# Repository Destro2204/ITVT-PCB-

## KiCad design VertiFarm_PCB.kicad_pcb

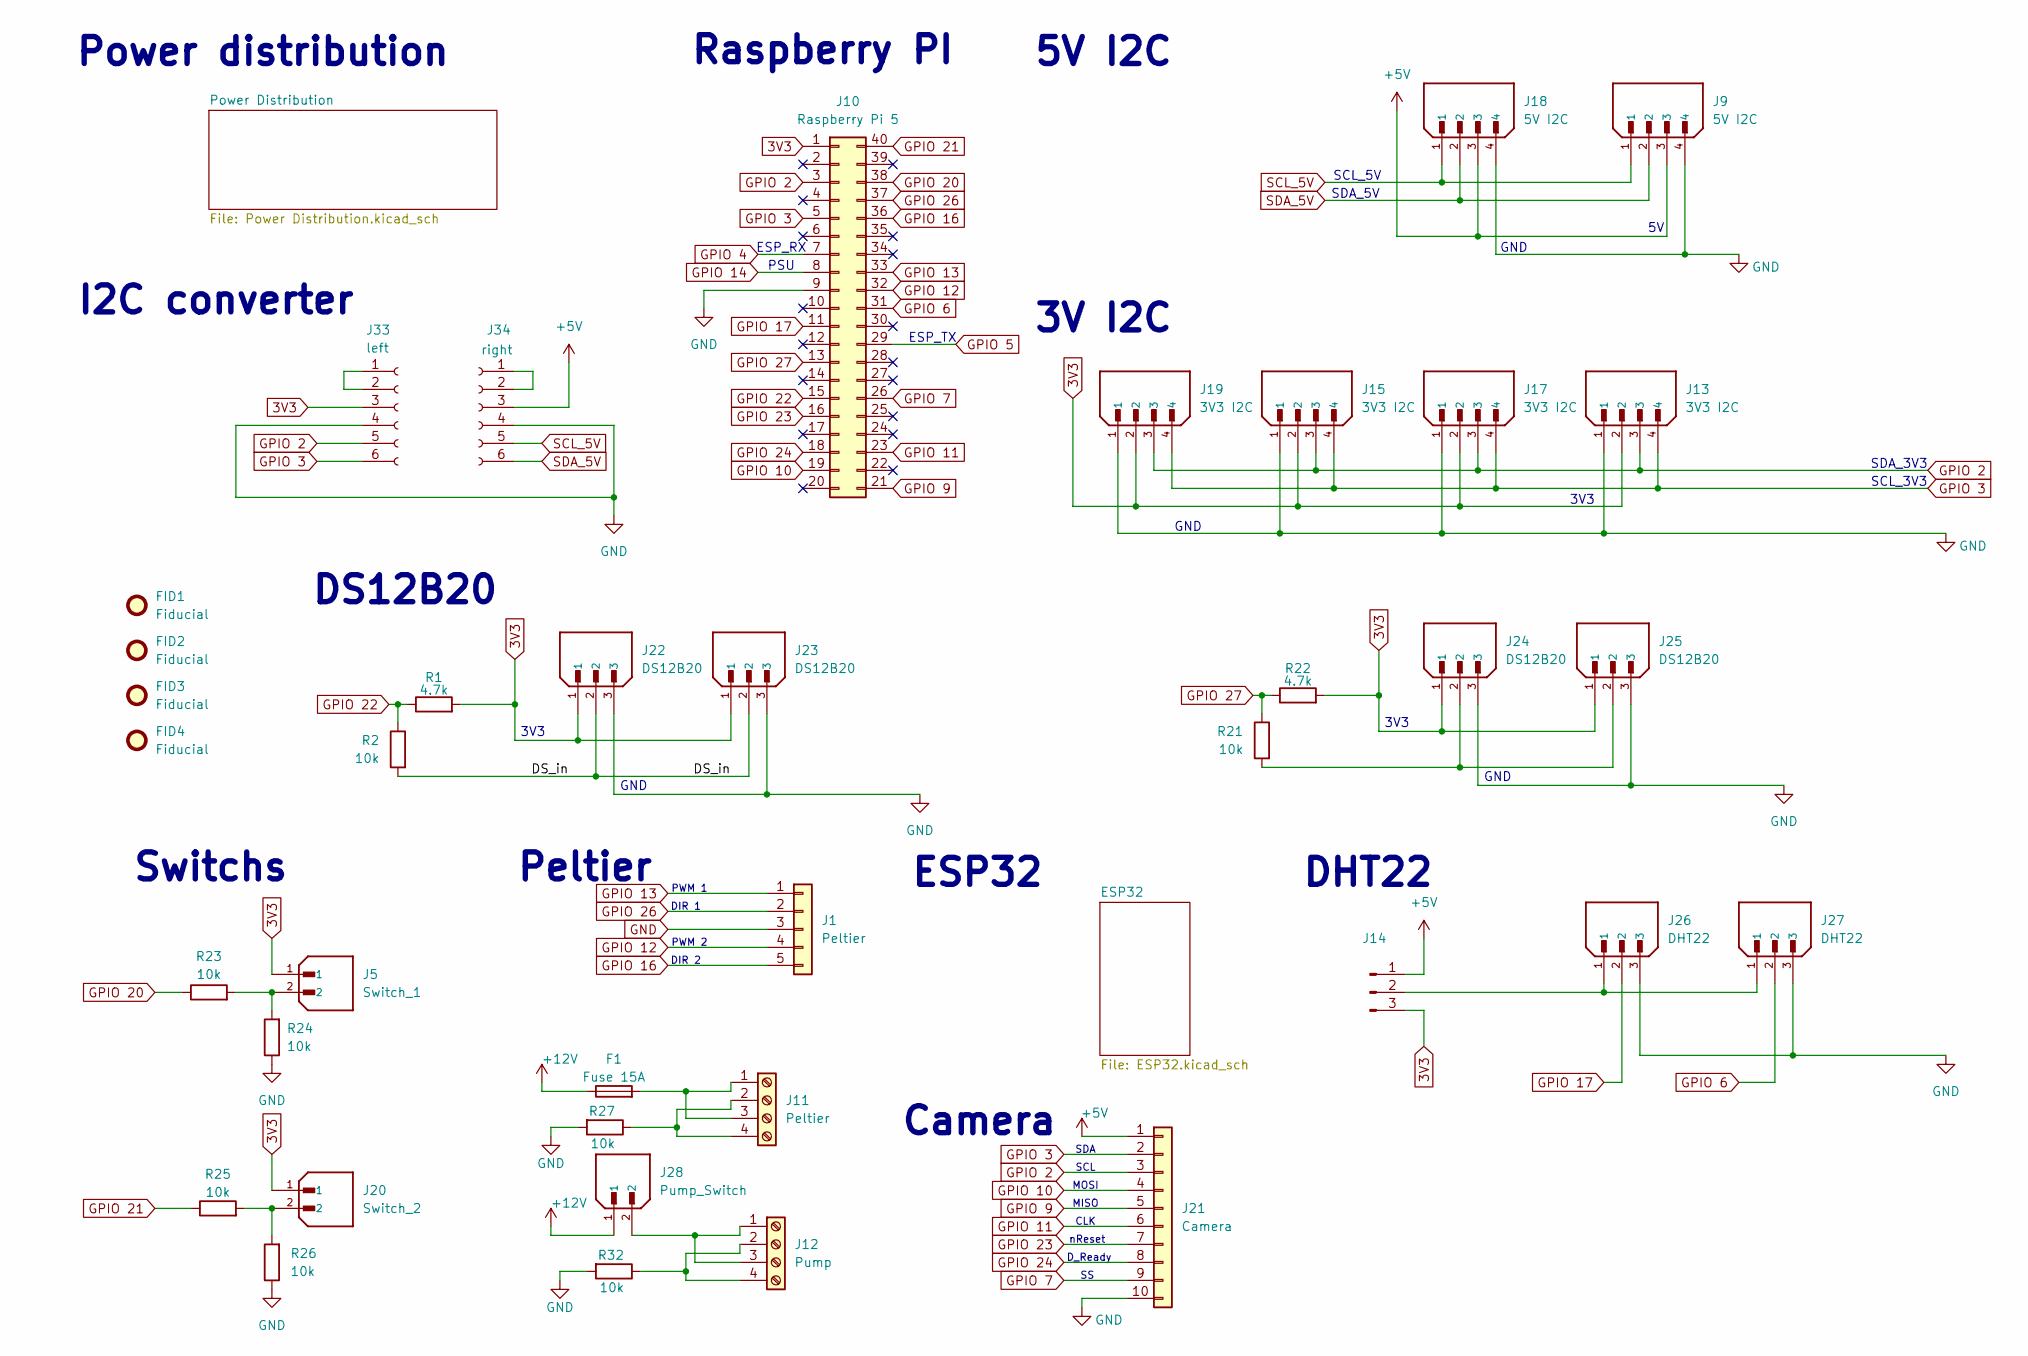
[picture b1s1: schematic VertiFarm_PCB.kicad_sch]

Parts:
F1: Fuse 15A; 35222_FH
FID1, FID2, FID3, FID4: Fiducial; Fiducial_0.75mm_Mask1.5mm
J1: Peltier; PinHeader_1x05_P2.54mm_Vertical
J5: Switch_1; JST_XH_B2B-XH-A_1x02_P2.50mm_Vertical; PARTREV N/A
J9: 5V I2C; JST_XH_B4B-XH-A_1x04_P2.50mm_Vertical; PARTREV 7/4/21
J10: Raspberry Pi 5; PinHeader_2x20_P2.54mm_Vertical
J11: Peltier; PhoenixContact_MSTBA_2,5_4-G-5,08_1x04_P5.08mm_Horizontal
J12: Pump; PhoenixContact_MSTBA_2,5_4-G-5,08_1x04_P5.08mm_Horizontal
J13, J17: 3V3 I2C; JST_XH_B4B-XH-A_1x04_P2.50mm_Vertical; PARTREV 7/4/21
J14: Conn_01x03_Pin; PinHeader_1x03_P2.54mm_Vertical
J15, J19: 3V3 I2C; NS-Tech_Grove_1x04_P2mm_Vertical; PARTREV 7/4/21
J18: 5V I2C; NS-Tech_Grove_1x04_P2mm_Vertical; PARTREV 7/4/21
J20: Switch_2; JST_XH_B2B-XH-A_1x02_P2.50mm_Vertical; PARTREV N/A
J21: Camera; PinHeader_1x10_P2.54mm_Vertical
J22, J23, J24, J25: DS12B20; JST_XH_B3B-XH-A_1x03_P2.50mm_Vertical; PARTREV 7/4/21
J26, J27: DHT22; JST_XH_B3B-XH-A_1x03_P2.50mm_Vertical; PARTREV 7/4/21
J28: Pump_Switch; JST_XH_B2B-XH-A_1x02_P2.50mm_Vertical; PARTREV N/A
J33: left; PinHeader_1x06_P2.54mm_Vertical
J34: right; PinHeader_1x06_P2.54mm_Vertical
R1, R22: 4.7k; R_Axial_DIN0207_L6.3mm_D2.5mm_P10.16mm_Horizontal
R2, R21, R23, R24, R25, R26, R27, R32: 10k; R_Axial_DIN0207_L6.3mm_D2.5mm_P10.16mm_Horizontal

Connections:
3V3: J5.1, J10.1, J13.2, J14.3, J15.2, J17.2, J19.2, J20.1, J22.1, J23.1, J24.1, J25.1, J33.3, R1.2, R22.2
+5V: J9.3, J14.1, J18.3, J21.1, J34.3; also elsewhere on the board
+12V: F1.1, J28.1; also elsewhere on the board
/DS_in: J22.2, J23.2, R2.2
GND: J1.3, J9.4, J10.9, J13.1, J15.1, J17.1, J18.4, J19.1, J21.10, J22.3, J23.3, J24.3, J25.3, J26.3, J27.3, J33.4, J34.4, R24.1, R26.1, R27.2, R32.2; also elsewhere on the board
GPIO 2: J10.3, J13.3, J15.3, J17.3, J19.3, J21.3, J33.5
GPIO 3: J10.5, J13.4, J15.4, J17.4, J19.4, J21.2, J33.6
GPIO 4: J10.7; also elsewhere on the board
GPIO 5: J10.29; also elsewhere on the board
GPIO 6: J10.31, J27.2
GPIO 7: J10.26, J21.9
GPIO 9: J10.21, J21.5
GPIO 10: J10.19, J21.4
GPIO 11: J10.23, J21.6
GPIO 12: J1.4, J10.32
GPIO 13: J1.1, J10.33
GPIO 14: J10.8; also elsewhere on the board
GPIO 16: J1.5, J10.36
GPIO 17: J10.11, J26.2
GPIO 20: J10.38, R23.1
GPIO 21: J10.40, R25.1
GPIO 22: J10.15, R1.1, R2.1
GPIO 23: J10.16, J21.7
GPIO 24: J10.18, J21.8
GPIO 26: J1.2, J10.37
GPIO 27: J10.13, R21.1, R22.1
unnamed: J5.2, R23.2, R24.2
unnamed: F1.2, J11.1, J11.3
unnamed: J11.2, J11.4, R27.1
unnamed: J12.1, J12.3, J28.2
unnamed: J12.2, J12.4, R32.1
unnamed: J14.2, J26.1, J27.1
unnamed: J20.2, R25.2, R26.2
unnamed: J24.2, J25.2, R21.2
unnamed: J33.1, J33.2
unnamed: J34.1, J34.2
SCL_5V: J9.1, J18.1, J34.5
SDA_5V: J9.2, J18.2, J34.6

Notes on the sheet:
DIR 2
5V I2C
3V3
GND
PSU
3V I2C
ESP32
SDA
nReset
Raspberry PI
PWM 1
PWM 2
CLK
SDA_3V3
SCL_5V
Power distribution
Switchs
D_Ready
Camera
ESP_RX
SCL
Peltier
DIR 1
DHT22
SCL_3V3
SDA_5V
ESP_TX
MOSI
MISO
I2C converter
DS12B20

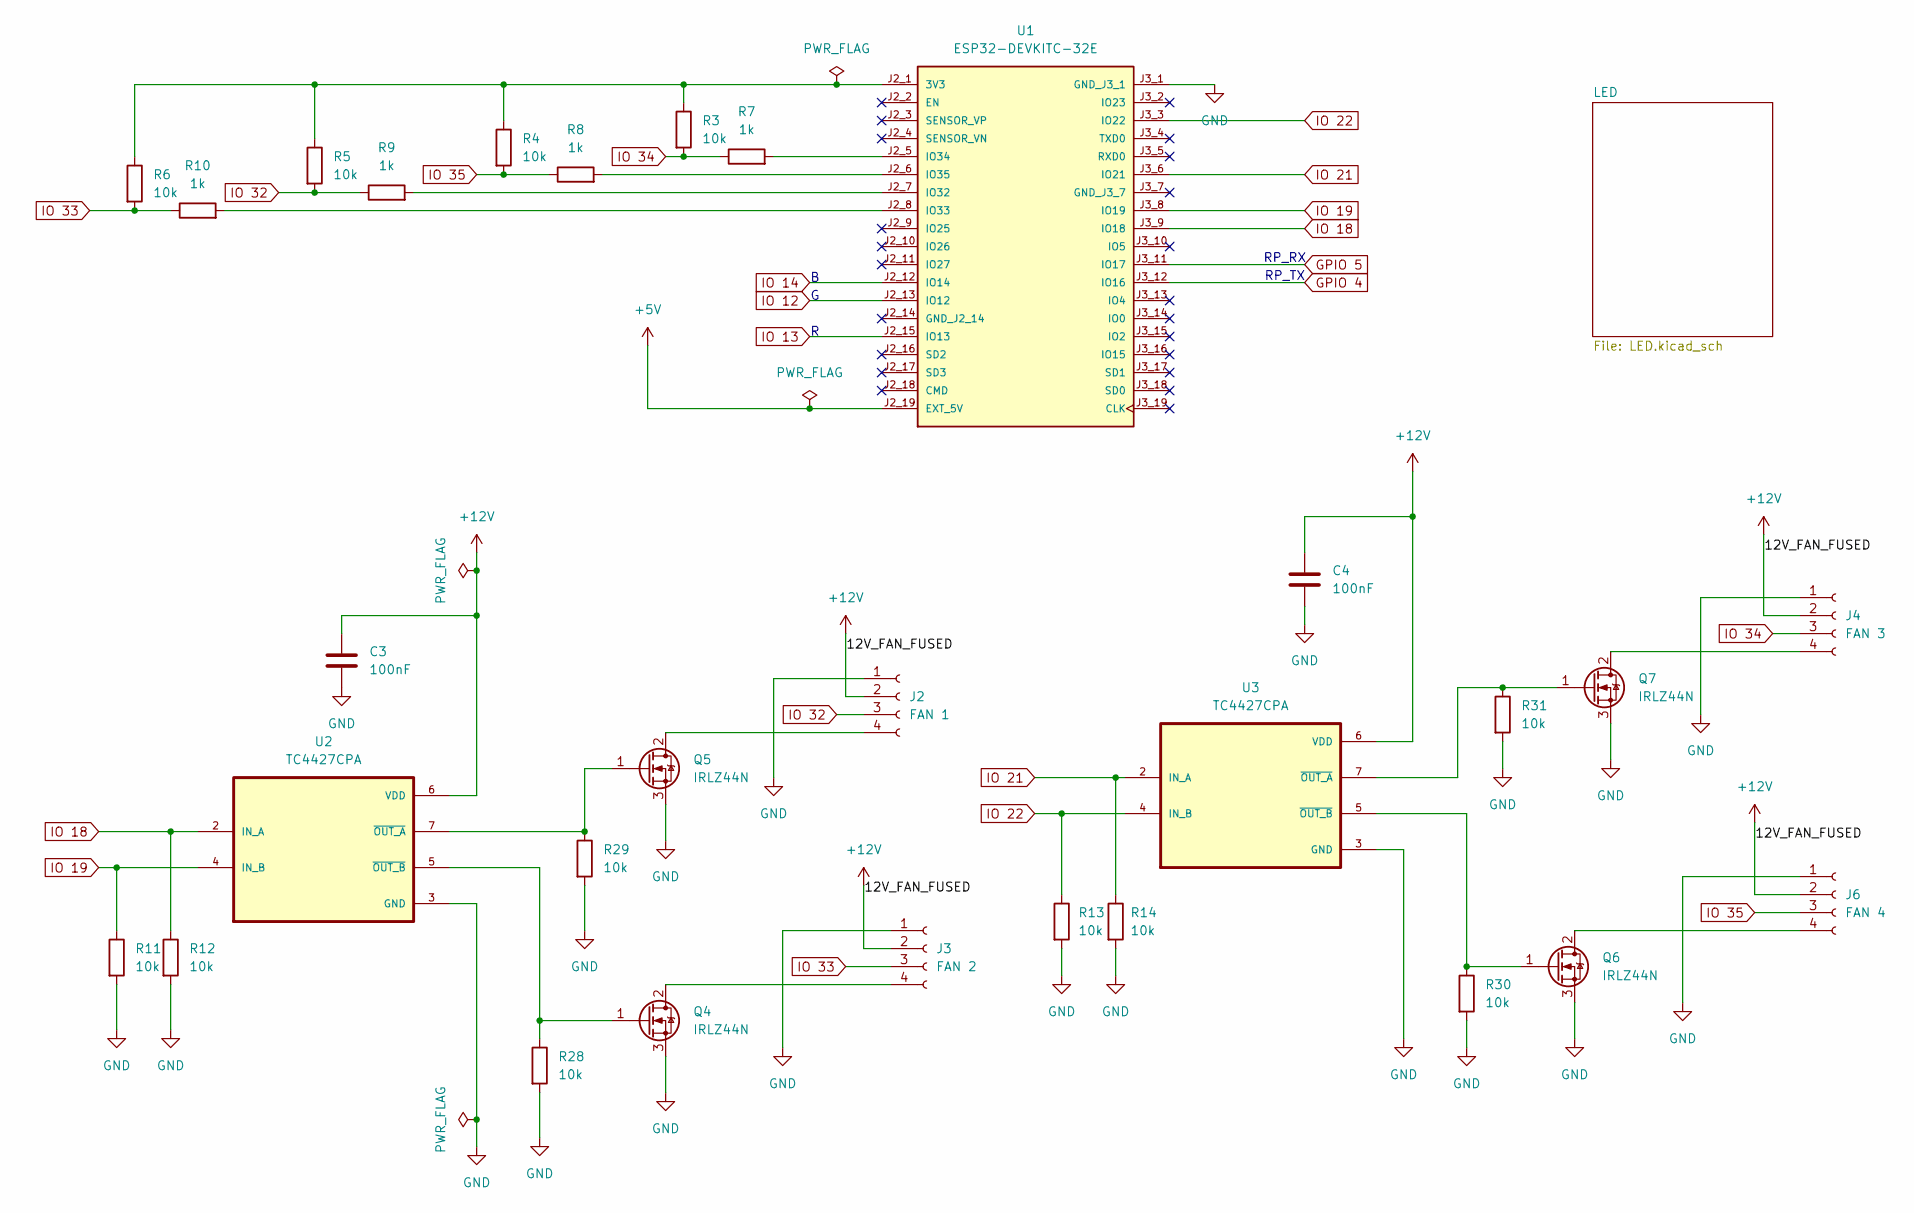
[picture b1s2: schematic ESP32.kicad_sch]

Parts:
C3, C4: 100nF; C_Disc_D5.0mm_W2.5mm_P5.00mm
J2: FAN 1; FanPinHeader_1x04_P2.54mm_Vertical
J3: FAN 2; FanPinHeader_1x04_P2.54mm_Vertical
J4: FAN 3; FanPinHeader_1x04_P2.54mm_Vertical
J6: FAN 4; FanPinHeader_1x04_P2.54mm_Vertical
Q4, Q5, Q6, Q7: IRLZ44N; TO-220-3_Vertical
R3, R4, R5, R6, R11, R12, R13, R14, R28, R29, R30, R31: 10k; R_Axial_DIN0207_L6.3mm_D2.5mm_P10.16mm_Horizontal
R7, R8, R9, R10: 1k; R_Axial_DIN0207_L6.3mm_D2.5mm_P10.16mm_Horizontal
U1: ESP32-DEVKITC-32E; MODULE_ESP32-DEVKITC-32E; PARTREV 1.4
U2, U3: TC4427CPA; DIP794W46P254L978H432Q8; PARTREV LTR

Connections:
+5V: U1.J2_19 (EXT_5V); also elsewhere on the board
+12V: C3.1, C4.1, J2.2, J3.2, J4.2, J6.2, U2.6 (VDD), U3.6 (VDD); also elsewhere on the board
GND: C3.2, C4.2, J2.1, J3.1, J4.1, J6.1, Q4.3 (S), Q5.3 (S), Q6.3 (S), Q7.3 (S), R11.2, R12.2, R13.2, R14.2, R28.2, R29.2, R30.2, R31.2, U1.J3_1 (GND_J3_1), U2.3 (GND), U3.3 (GND); also elsewhere on the board
GPIO 4: U1.J3_12 (IO16); also elsewhere on the board
GPIO 5: U1.J3_11 (IO17); also elsewhere on the board
IO 12: U1.J2_13 (IO12); also elsewhere on the board
IO 13: U1.J2_15 (IO13); also elsewhere on the board
IO 14: U1.J2_12 (IO14); also elsewhere on the board
IO 18: R12.1, U1.J3_9 (IO18), U2.2 (IN_A)
IO 19: R11.1, U1.J3_8 (IO19), U2.4 (IN_B)
IO 21: R14.1, U1.J3_6 (IO21), U3.2 (IN_A)
IO 22: R13.1, U1.J3_3 (IO22), U3.4 (IN_B)
IO 32: J2.3, R5.2, R9.1
IO 33: J3.3, R6.2, R10.1
IO 34: J4.3, R3.2, R7.1
IO 35: J6.3, R4.2, R8.1
unnamed: J2.4, Q5.2 (D)
unnamed: J3.4, Q4.2 (D)
unnamed: J4.4, Q7.2 (D)
unnamed: J6.4, Q6.2 (D)
unnamed: Q4.1 (G), R28.1, U2.5 (~OUT_B)
unnamed: Q5.1 (G), R29.1, U2.7 (~OUT_A)
unnamed: Q6.1 (G), R30.1, U3.5 (~OUT_B)
unnamed: Q7.1 (G), R31.1, U3.7 (~OUT_A)
unnamed: R3.1, R4.1, R5.1, R6.1, U1.J2_1 (3V3)
unnamed: R9.2, U1.J2_7 (IO32)
unnamed: R10.2, U1.J2_8 (IO33)
unnamed: R7.2, U1.J2_5 (IO34)
unnamed: R8.2, U1.J2_6 (IO35)

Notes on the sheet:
RP_TX
RP_RX

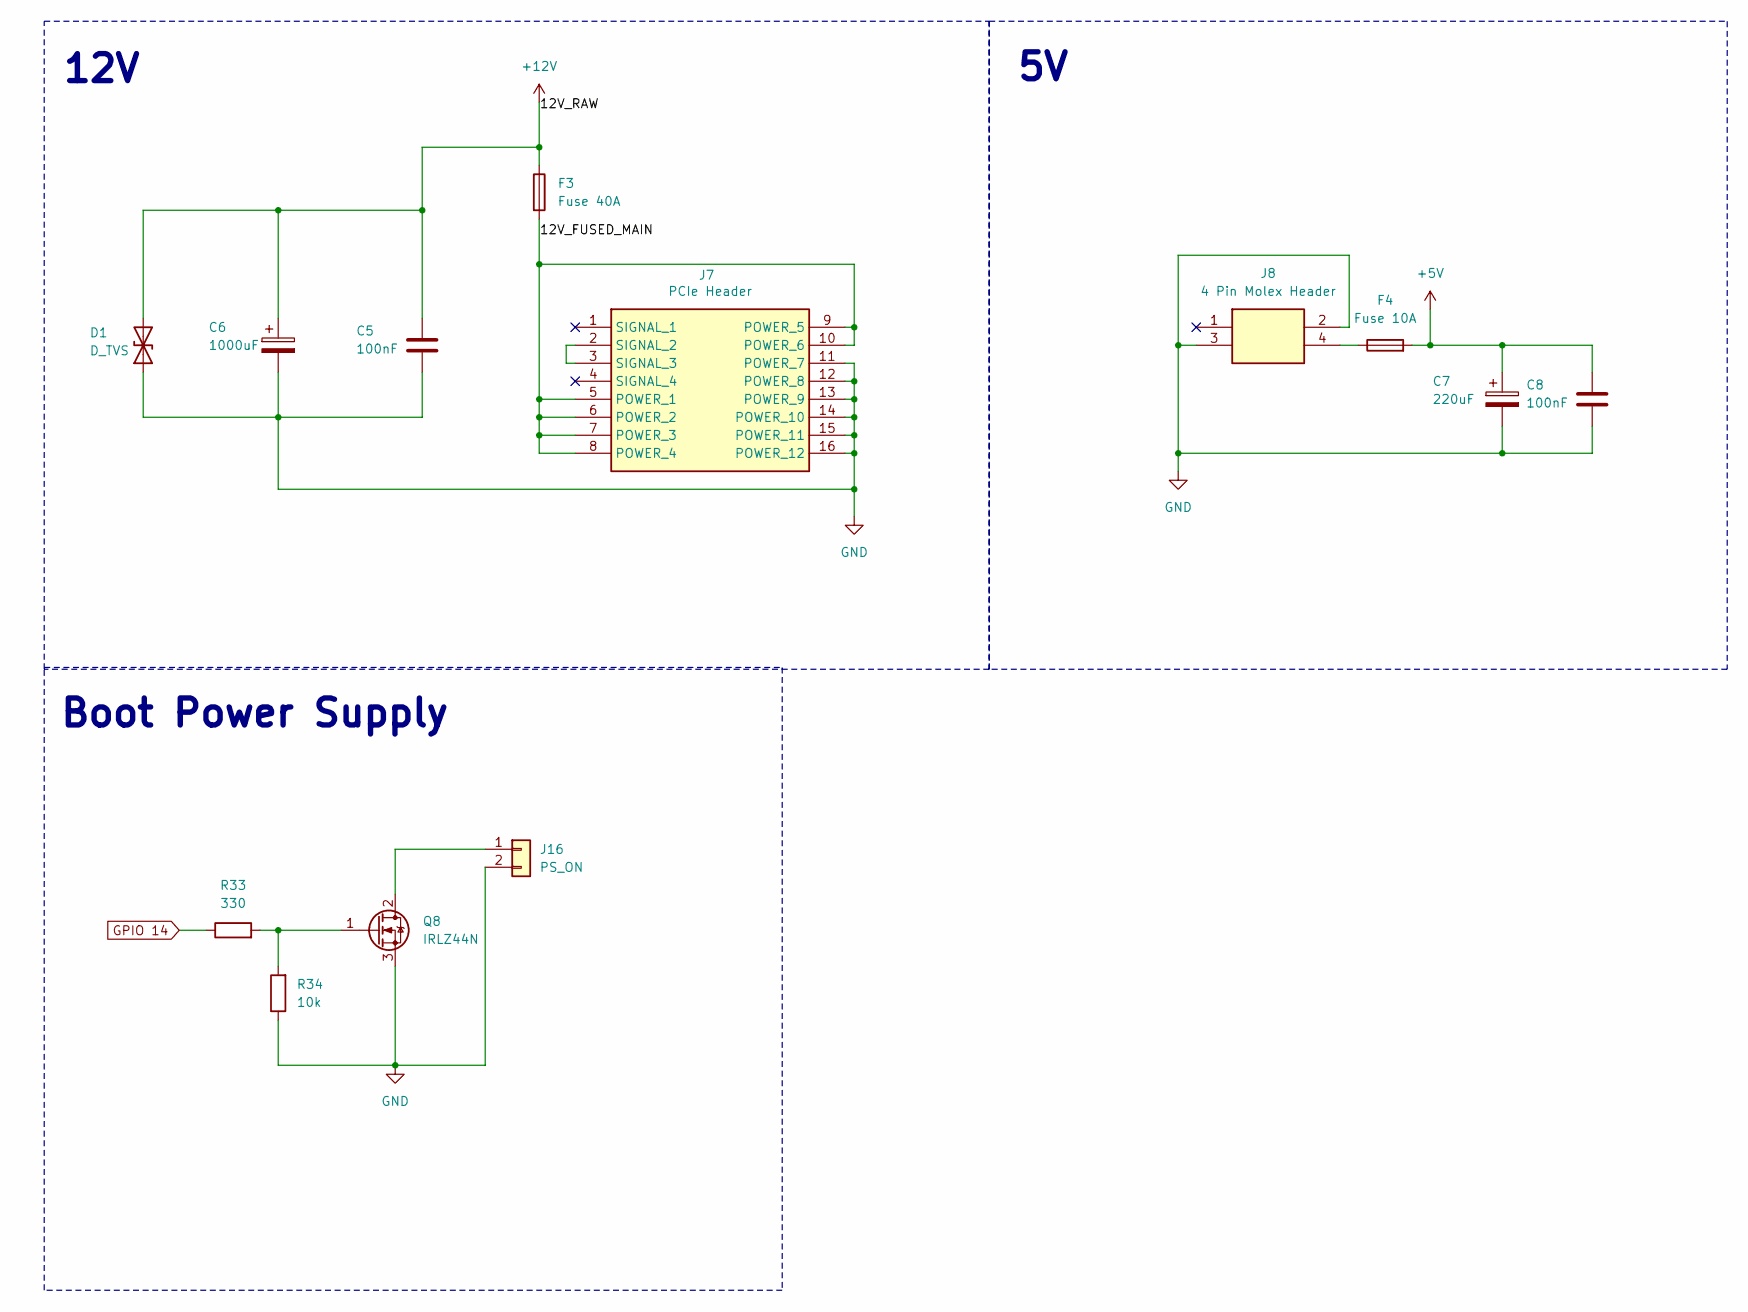
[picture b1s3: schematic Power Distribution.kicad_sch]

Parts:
C5, C8: 100nF; C_Disc_D5.0mm_W2.5mm_P5.00mm
C6: 1000uF; CP_Radial_D10.0mm_P5.00mm
C7: 220uF; CP_Radial_D10.0mm_P5.00mm
D1: D_TVS; D_DO-201_P15.24mm_Horizontal
F3: Fuse 40A; 35222_FH
F4: Fuse 10A; 35222_FH
J7: PCIe Header; 2191160161; Manufacturer_Part_Number 219116-0161; Mouser Part Number 538-219116-0161
J8: 4 Pin Molex Header; New_4Pin_Molex; Manufacturer_Part_Number 231-834/001-000/105-604
J16: PS_ON; PinHeader_1x02_P2.54mm_Vertical
Q8: IRLZ44N; TO-220-3_Vertical
R33: 330; R_Axial_DIN0207_L6.3mm_D2.5mm_P10.16mm_Horizontal
R34: 10k; R_Axial_DIN0207_L6.3mm_D2.5mm_P10.16mm_Horizontal

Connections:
+5V: C7.1, C8.1, F4.2; also elsewhere on the board
+12V: C5.1, C6.1, D1.2 (A2), F3.1; also elsewhere on the board
/Power Distribution/12V_FUSED_MAIN: F3.2, J7.5 (POWER_1), J7.6 (POWER_2), J7.7 (POWER_3), J7.8 (POWER_4), J7.9 (POWER_5), J7.10 (POWER_6)
GND: C5.2, C6.2, C7.2, C8.2, D1.1 (A1), J7.11 (POWER_7), J7.12 (POWER_8), J7.13 (POWER_9), J7.14 (POWER_10), J7.15 (POWER_11), J7.16 (POWER_12), J8.2, J8.3, J16.2, Q8.3 (S), R34.1; also elsewhere on the board
GPIO 14: R33.1; also elsewhere on the board
unnamed: F4.1, J8.4
unnamed: J7.2 (SIGNAL_2), J7.3 (SIGNAL_3)
unnamed: J16.1, Q8.2 (D)
unnamed: Q8.1 (G), R33.2, R34.2

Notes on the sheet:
Boot Power Supply
12V

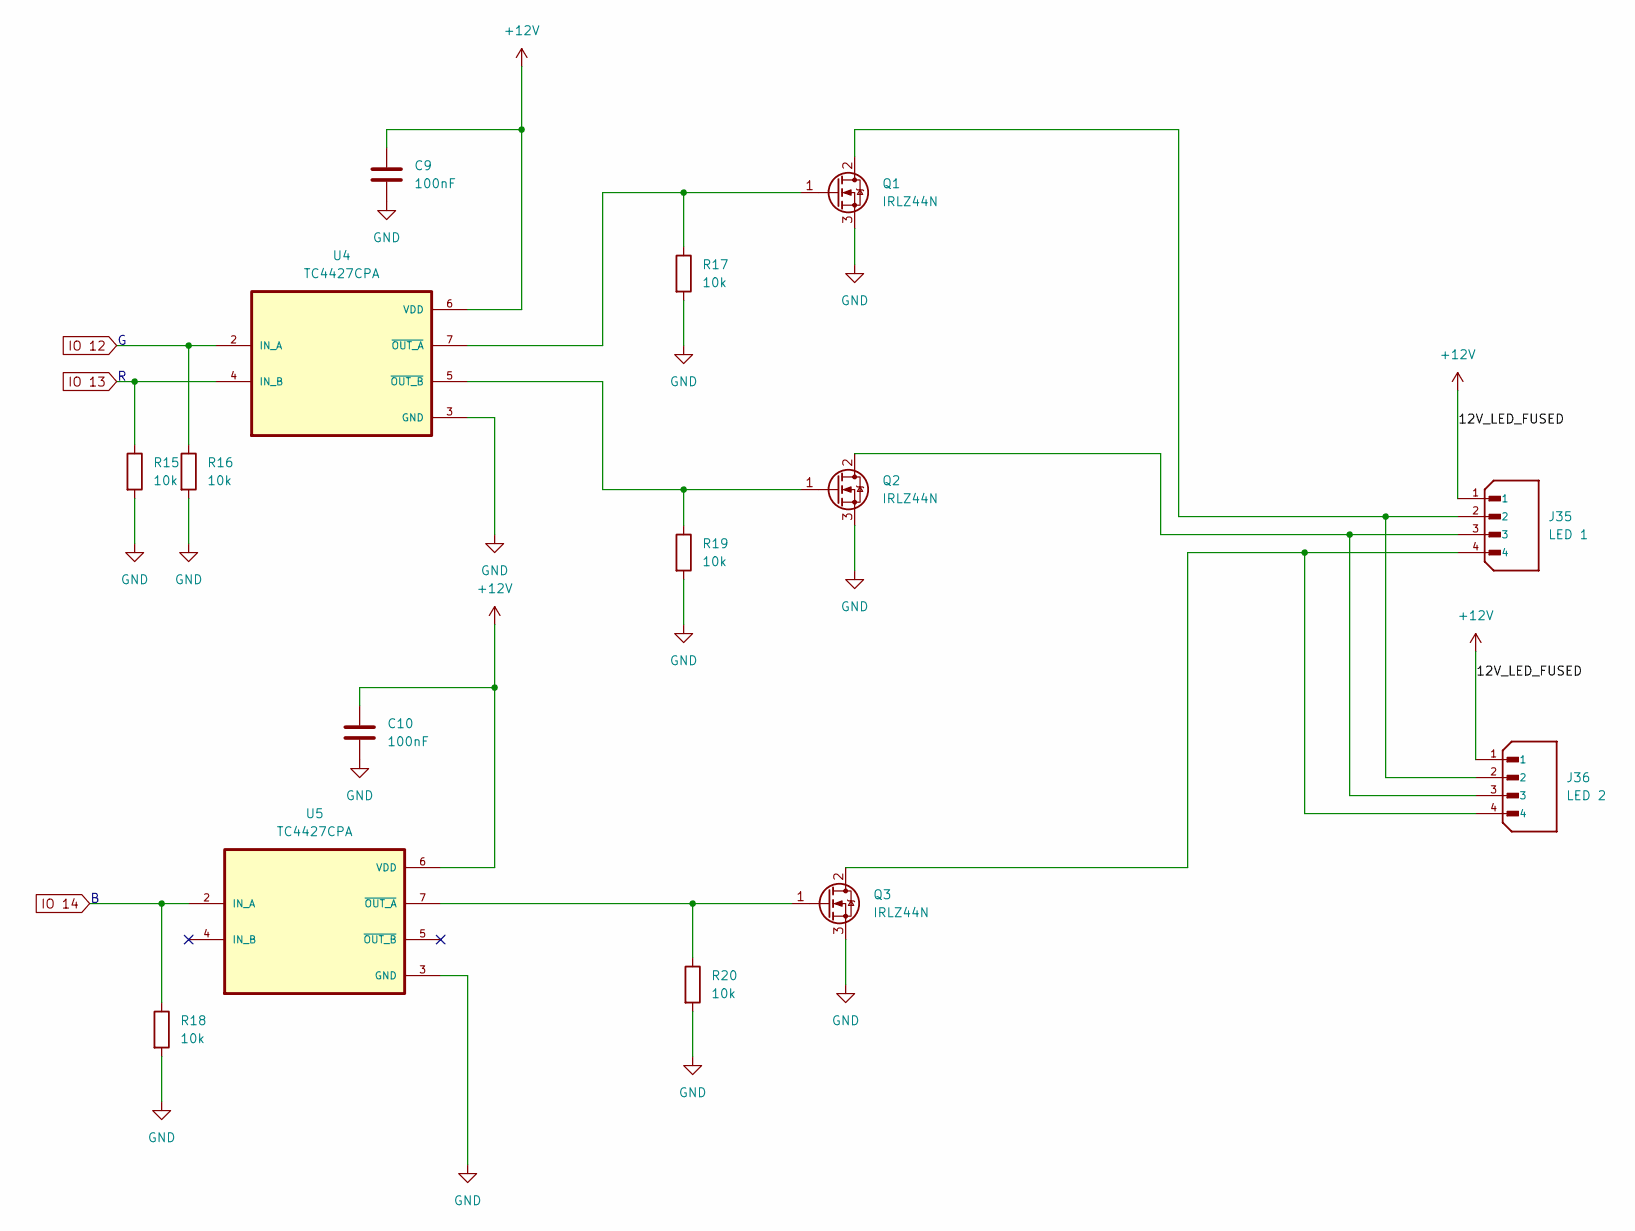
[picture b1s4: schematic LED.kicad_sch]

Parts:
C9, C10: 100nF; C_Disc_D5.0mm_W2.5mm_P5.00mm
J35: LED 1; JST_B4B-XH-A_LF__SN_; PARTREV 7/4/21
J36: LED 2; JST_B4B-XH-A_LF__SN_; PARTREV 7/4/21
Q1, Q2, Q3: IRLZ44N; TO-220-3_Vertical
R15, R16, R17, R18, R19, R20: 10k; R_Axial_DIN0207_L6.3mm_D2.5mm_P10.16mm_Horizontal
U4, U5: TC4427CPA; DIP794W46P254L978H432Q8; PARTREV LTR

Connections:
+12V: C9.1, C10.1, J35.1, J36.1, U4.6 (VDD), U5.6 (VDD); also elsewhere on the board
GND: C9.2, C10.2, Q1.3 (S), Q2.3 (S), Q3.3 (S), R15.2, R16.2, R17.2, R18.2, R19.2, R20.2, U4.3 (GND), U5.3 (GND); also elsewhere on the board
IO 12: R16.1, U4.2 (IN_A); also elsewhere on the board
IO 13: R15.1, U4.4 (IN_B); also elsewhere on the board
IO 14: R18.1, U5.2 (IN_A); also elsewhere on the board
unnamed: J35.2, J36.2, Q1.2 (D)
unnamed: Q1.1 (G), R17.1, U4.7 (~OUT_A)
unnamed: J35.3, J36.3, Q2.2 (D)
unnamed: Q2.1 (G), R19.1, U4.5 (~OUT_B)
unnamed: J35.4, J36.4, Q3.2 (D)
unnamed: Q3.1 (G), R20.1, U5.7 (~OUT_A)

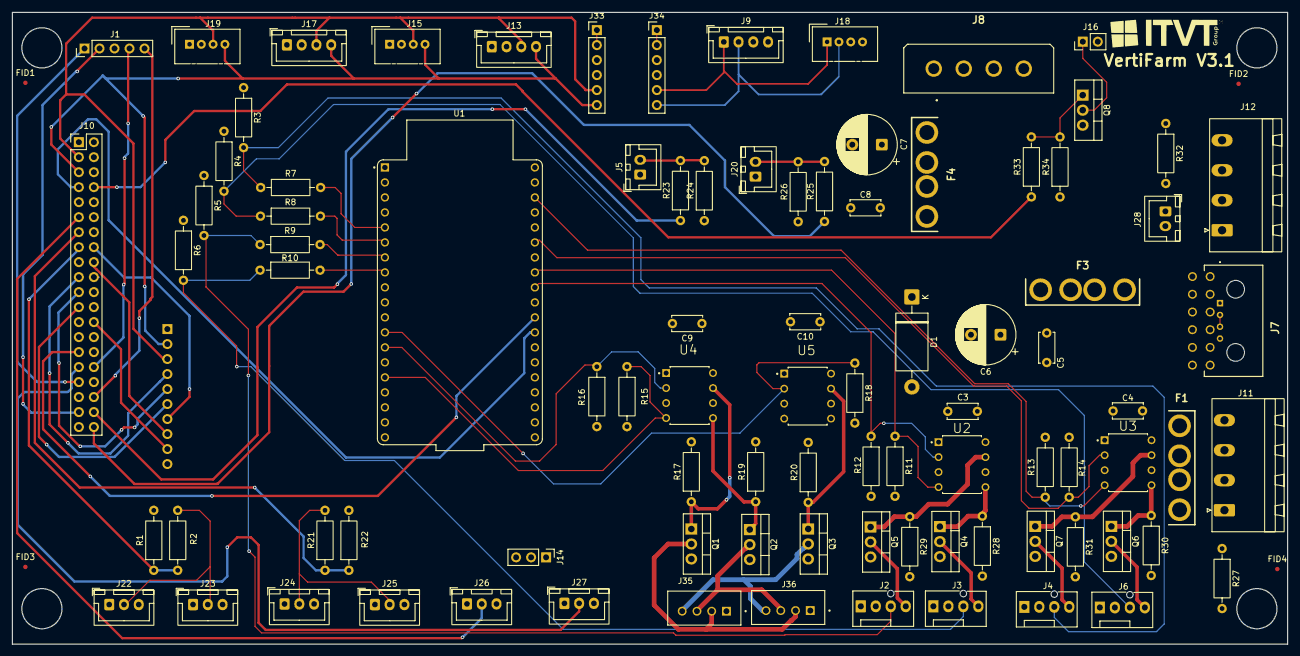
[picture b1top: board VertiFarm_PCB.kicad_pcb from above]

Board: 4 copper layers, 216.0 x 107.0 mm, 95 parts (1 on the bottom side), 73 nets.

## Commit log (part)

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2026-06-02 updated 1.0
2026-06-04 Describe the task you completed
2026-06-04 Local changes
2026-06-30 Gerber Files
2026-06-30 Missing libraries
2026-06-30 Net names
2026-06-30 compressed gerber files
2026-06-30 version 1.0
